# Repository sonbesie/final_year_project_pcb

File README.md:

# Final Year Project: Printed Circuit Board (PCB)

## Description
The PCB’s for my final year project. The repository contains two folders each containing a PCB. The first PCB is the camera board where all the cameras monitoring the finish line are attached. The second PCB contains the designs for the memory card.

## Open
To open the project download KiCad and open the .pro file.

## Image

A render of the first PCB is provided below:

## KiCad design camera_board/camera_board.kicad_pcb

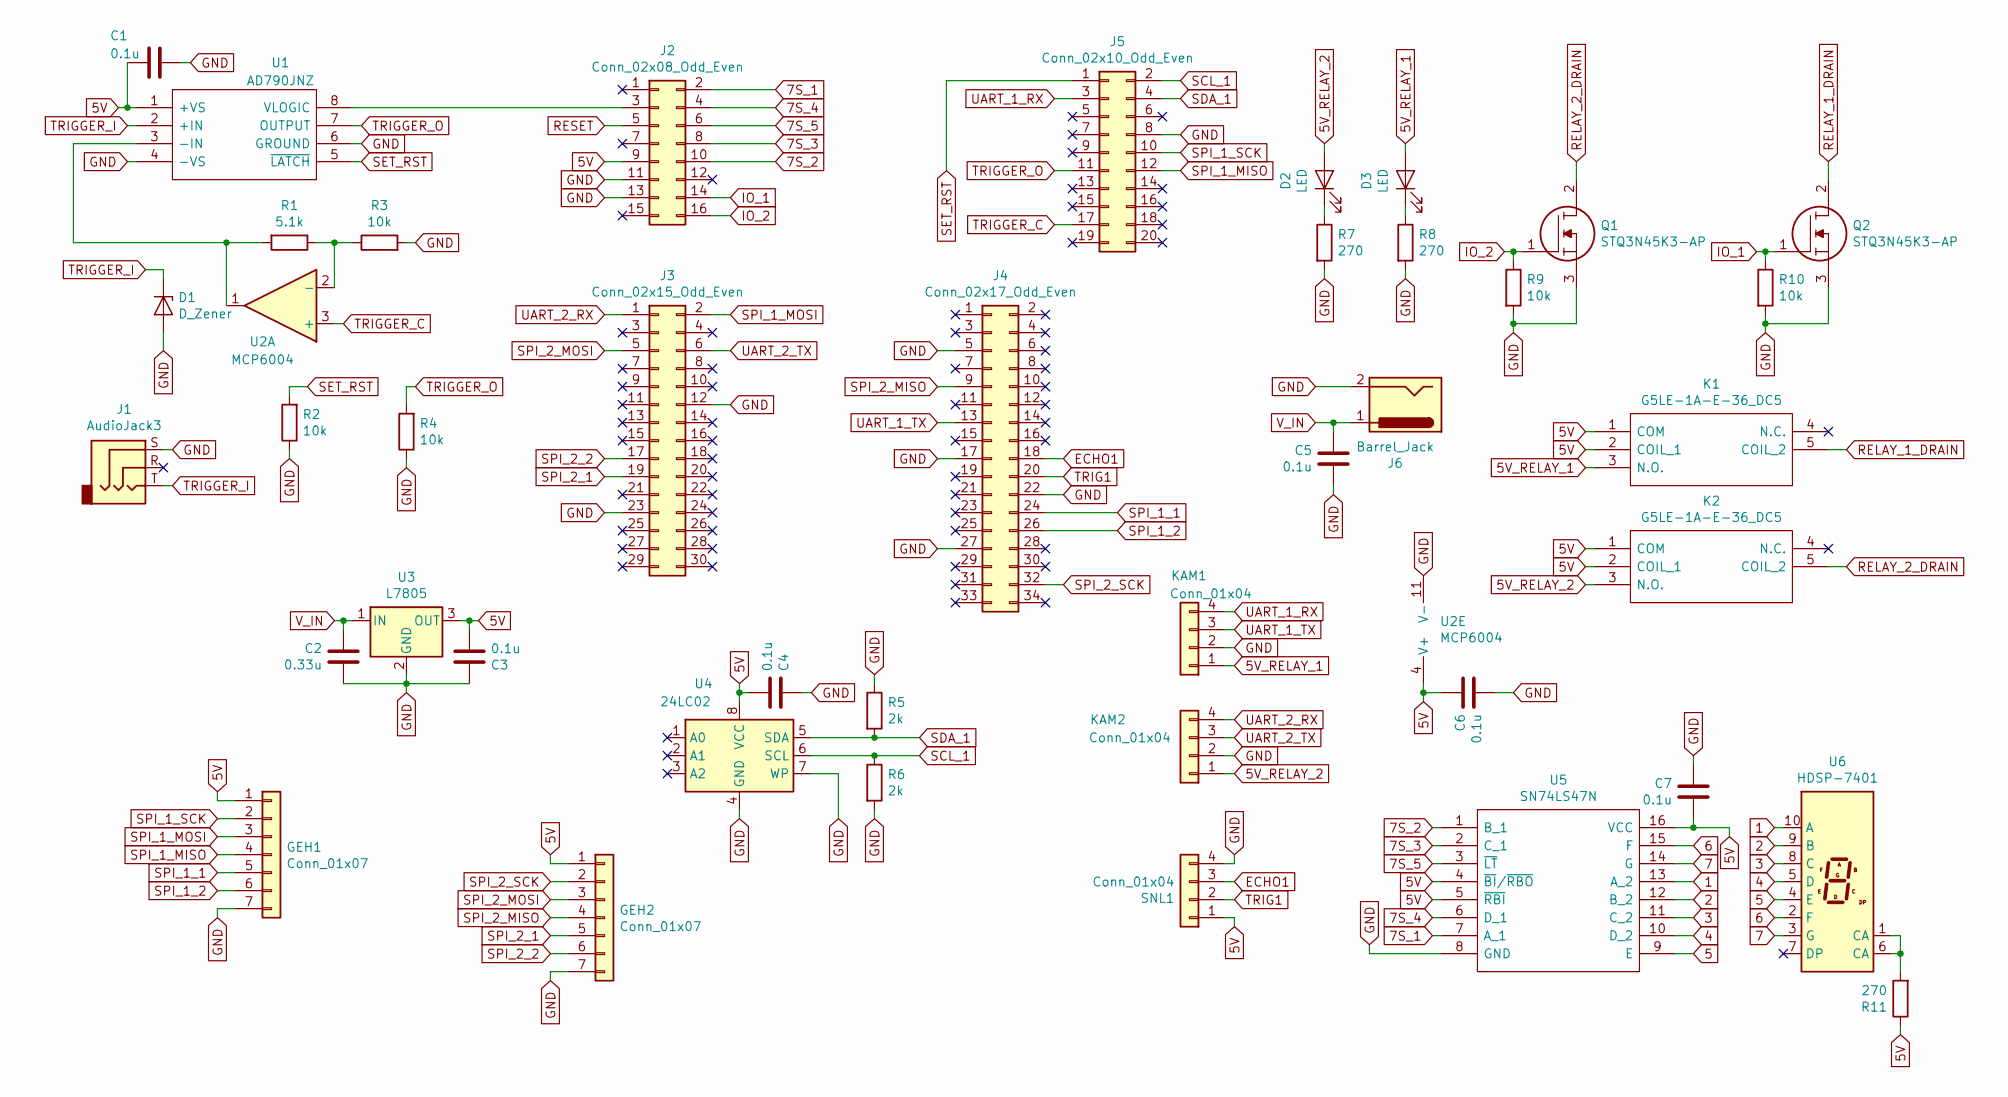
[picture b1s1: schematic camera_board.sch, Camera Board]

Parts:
C1, C3, C4, C5, C6, C7: 0.1u; C_Disc_D5.0mm_W2.5mm_P2.50mm
C2: 0.33u; C_Disc_D5.0mm_W2.5mm_P2.50mm
D1: D_Zener; D_DO-35_SOD27_P2.54mm_Vertical_AnodeUp
D2, D3: LED; LED_D3.0mm
GEH1, GEH2: Conn_01x07; JST_PH_B7B-PH-K_1x07_P2.00mm_Vertical
J1: AudioJack3; Jack_3.5mm_CUI_SJ1-3533NG_Horizontal
J2: Conn_02x08_Odd_Even; PinHeader_2x08_P2.54mm_Vertical
J3: Conn_02x15_Odd_Even; PinHeader_2x15_P2.54mm_Vertical
J4: Conn_02x17_Odd_Even; PinHeader_2x17_P2.54mm_Vertical
J5: Conn_02x10_Odd_Even; PinHeader_2x10_P2.54mm_Vertical
J6: Barrel_Jack; BarrelJack_CUI_PJ-063AH_Horizontal
K1, K2: G5LE-1A-E-36_DC5; G5LE1AE36DC5; Manufacturer_Part_Number G5LE-1A-E-36 DC5; Mouser Part Number 653-G5LE-1A-E-36DC5
KAM1, KAM2: Conn_01x04; JST_PH_B4B-PH-K_1x04_P2.00mm_Vertical
Q1, Q2: STQ3N45K3-AP; TO-92_Inline_Wide; Manufacturer_Part_Number STQ3N45K3-AP; Mouser Part Number 511-STQ3N45K3-AP
R1: 5.1k; R_Axial_DIN0207_L6.3mm_D2.5mm_P7.62mm_Horizontal
R2, R3, R4, R9, R10: 10k; R_Axial_DIN0207_L6.3mm_D2.5mm_P7.62mm_Horizontal
R5, R6: 2k; R_Axial_DIN0207_L6.3mm_D2.5mm_P7.62mm_Horizontal
R7, R8, R11: 270; R_Axial_DIN0207_L6.3mm_D2.5mm_P7.62mm_Horizontal
SNL1: Conn_01x04; JST_PH_B4B-PH-K_1x04_P2.00mm_Vertical
U1: AD790JNZ; DIP-8_W7.62mm; Manufacturer_Part_Number AD790JNZ; Mouser Part Number 584-AD790JNZ
U2: MCP6004; DIP-14_W7.62mm
U3: L7805; TO-220-3_Vertical
U4: 24LC02; DIP-8_W7.62mm
U5: SN74LS47N; DIP-16_W7.62mm; Manufacturer_Part_Number SN74LS47N; Mouser Part Number 595-SN74LS47N
U6: HDSP-7401

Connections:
1: U5.13 (A_2), U6.10 (A)
2: U5.12 (B_2), U6.9 (B)
3: U5.11 (C_2), U6.8 (C)
4: U5.10 (D_2), U6.5 (D)
5: U5.9 (E), U6.4 (E)
5V: C1.2, C3.2, C4.2, C6.1, C7.2, GEH1.1, GEH2.1, J2.9, K1.1 (COM), K1.2 (COIL_1), K2.1 (COM), K2.2 (COIL_1), R11.1, SNL1.1, U1.1 (+VS), U2.4 (V+), U3.3 (OUT), U4.8 (VCC), U5.4 (~BI~/~RBO), U5.5 (~RBI), U5.16 (VCC)
5V_RELAY_1: D3.2 (A), K1.3 (N.O.), KAM1.1
5V_RELAY_2: D2.2 (A), K2.3 (N.O.), KAM2.1
6: U5.15 (F), U6.2 (F)
7: U5.14 (G), U6.3 (G)
7S_1: J2.2, U5.7 (A_1)
7S_2: J2.10, U5.1 (B_1)
7S_3: J2.8, U5.2 (C_1)
7S_4: J2.4, U5.6 (D_1)
7S_5: J2.6, U5.3 (~LT)
ECHO1: J4.18, SNL1.3
GND: C1.1, C2.2, C3.1, C4.1, C5.2, C6.2, C7.1, D1.2 (A), GEH1.7, GEH2.7, J1.S, J2.11, J2.13, J3.12, J3.23, J4.5, J4.17, J4.22, J4.27, J5.8, J6.2, KAM1.2, KAM2.2, Q1.3, Q2.3, R2.1, R3.2, R4.1, R5.1, R6.2, R7.2, R8.2, R9.2, R10.2, SNL1.4, U1.4 (-VS), U1.6 (GROUND), U2.11 (V-), U3.2 (GND), U4.4 (GND), U4.7 (WP), U5.8 (GND)
IO_1: J2.14, Q2.1, R10.1
IO_2: J2.16, Q1.1, R9.1
unnamed: D2.1 (K), R7.1
unnamed: D3.1 (K), R8.1
unnamed: J2.3, U1.8 (VLOGIC)
unnamed: R1.1, R3.1, U2.2 (-)
unnamed: R1.2, U1.3 (-IN), U2.1
unnamed: R11.2, U6.1 (CA), U6.6 (CA)
RELAY_1_DRAIN: K1.5 (COIL_2), Q2.2
RELAY_2_DRAIN: K2.5 (COIL_2), Q1.2
SCL_1: J5.2, R6.1, U4.6 (SCL)
SDA_1: J5.4, R5.2, U4.5 (SDA)
SET_RST: J5.1, R2.2, U1.5 (~LATCH)
SPI_1_1: GEH1.5, J4.24
SPI_1_2: GEH1.6, J4.26
SPI_1_MISO: GEH1.4, J5.12
SPI_1_MOSI: GEH1.3, J3.2
SPI_1_SCK: GEH1.2, J5.10
SPI_2_1: GEH2.5, J3.19
SPI_2_2: GEH2.6, J3.17
SPI_2_MISO: GEH2.4, J4.9
SPI_2_MOSI: GEH2.3, J3.5
SPI_2_SCK: GEH2.2, J4.32
TRIG1: J4.20, SNL1.2
TRIGGER_C: J5.17, U2.3 (+)
TRIGGER_I: D1.1 (K), J1.T, U1.2 (+IN)
TRIGGER_O: J5.11, R4.2, U1.7 (OUTPUT)
UART_1_RX: J5.3, KAM1.4
UART_1_TX: J4.13, KAM1.3
UART_2_RX: J3.1, KAM2.4
UART_2_TX: J3.6, KAM2.3
V_IN: C2.1, C5.1, J6.1, U3.1 (IN)

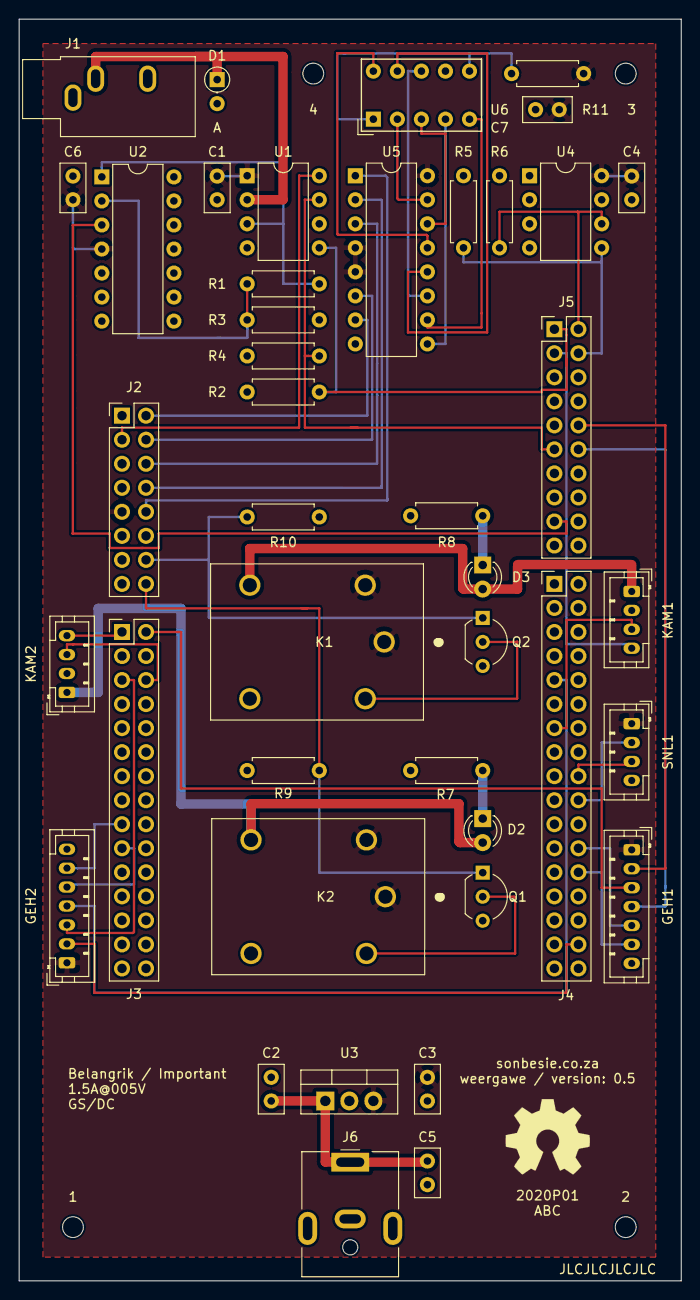
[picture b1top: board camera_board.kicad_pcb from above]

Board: 2 copper layers, 70.0 x 133.4 mm, 46 parts (0 on the bottom side), 49 nets.

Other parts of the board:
1, 2, 3, 4: MountingHole_2.2mm_M2

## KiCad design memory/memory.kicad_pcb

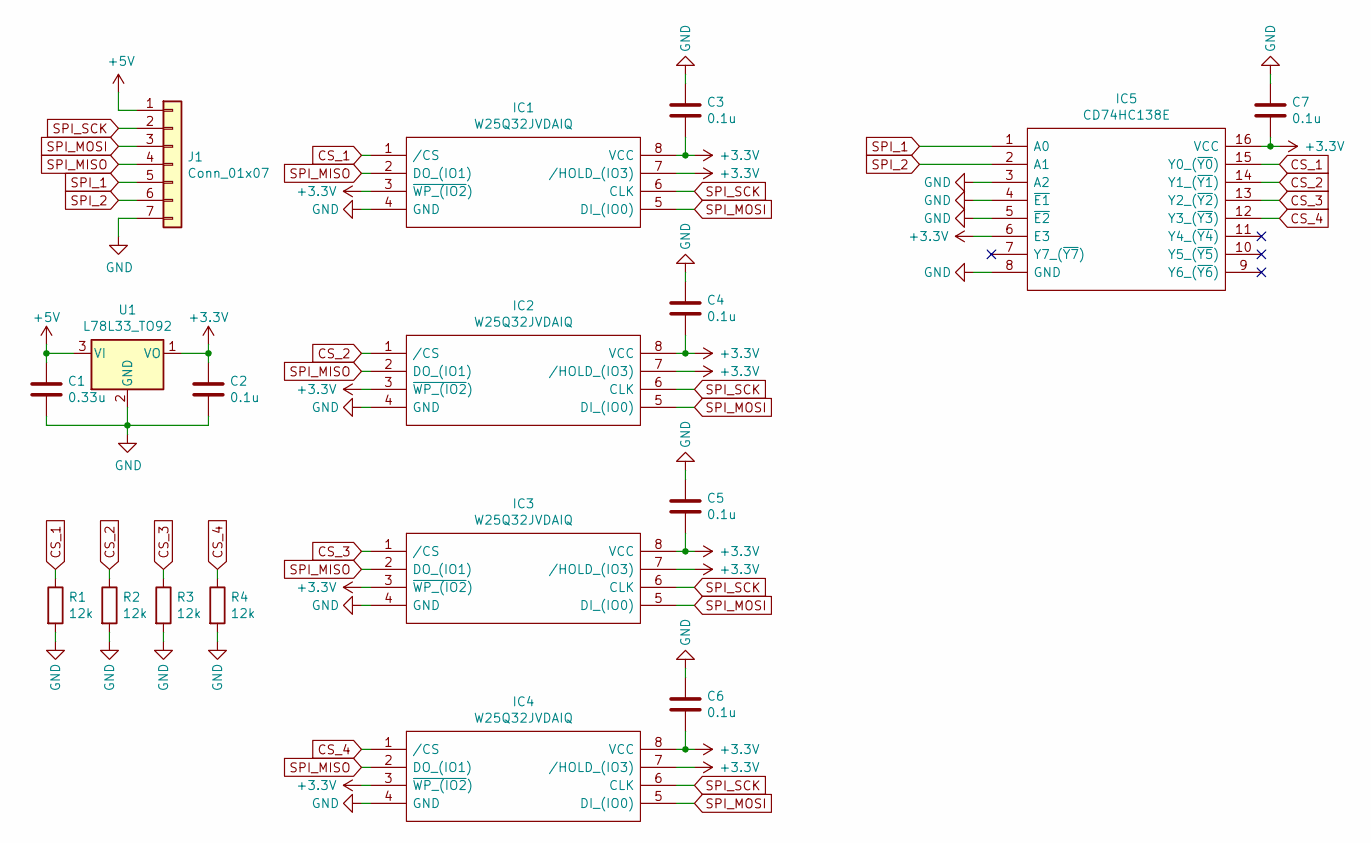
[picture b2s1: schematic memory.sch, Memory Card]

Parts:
C1: 0.33u; C_Disc_D5.0mm_W2.5mm_P2.50mm
C2, C3, C4, C5, C6, C7: 0.1u; C_Disc_D5.0mm_W2.5mm_P2.50mm
IC1, IC2, IC3, IC4: W25Q32JVDAIQ; DIP-8_W7.62mm; Manufacturer_Part_Number W25Q32JVDAIQ; Mouser Part Number 454-W25Q32JVDAIQ
IC5: CD74HC138E; DIP-16_W7.62mm; Manufacturer_Part_Number CD74HC138E; Mouser Part Number 595-CD74HC138E
J1: Conn_01x07; JST_PH_B7B-PH-K_1x07_P2.00mm_Vertical
R1, R2, R3, R4: 12k; R_Axial_DIN0207_L6.3mm_D2.5mm_P7.62mm_Horizontal
U1: L78L33_TO92; TO-92_Inline

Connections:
+3V3: C2.1, C3.2, C4.2, C5.2, C6.2, C7.2, IC1.3 (~WP_(IO2)), IC1.7 (/HOLD_(IO3)), IC1.8 (VCC), IC2.3 (~WP_(IO2)), IC2.7 (/HOLD_(IO3)), IC2.8 (VCC), IC3.3 (~WP_(IO2)), IC3.7 (/HOLD_(IO3)), IC3.8 (VCC), IC4.3 (~WP_(IO2)), IC4.7 (/HOLD_(IO3)), IC4.8 (VCC), IC5.6 (E3), IC5.16 (VCC), U1.1 (VO)
+5V: C1.1, J1.1, U1.3 (VI)
CS_1: IC1.1 (/CS), IC5.15 (Y0_(~Y0)), R1.1
CS_2: IC2.1 (/CS), IC5.14 (Y1_(~Y1)), R2.1
CS_3: IC3.1 (/CS), IC5.13 (Y2_(~Y2)), R3.1
CS_4: IC4.1 (/CS), IC5.12 (Y3_(~Y3)), R4.1
GND: C1.2, C2.2, C3.1, C4.1, C5.1, C6.1, C7.1, IC1.4 (GND), IC2.4 (GND), IC3.4 (GND), IC4.4 (GND), IC5.3 (A2), IC5.4 (~E1), IC5.5 (~E2), IC5.8 (GND), J1.7, R1.2, R2.2, R3.2, R4.2, U1.2 (GND)
SPI_1: IC5.1 (A0), J1.5
SPI_2: IC5.2 (A1), J1.6
SPI_MISO: IC1.2 (DO_(IO1)), IC2.2 (DO_(IO1)), IC3.2 (DO_(IO1)), IC4.2 (DO_(IO1)), J1.4
SPI_MOSI: IC1.5 (DI_(IO0)), IC2.5 (DI_(IO0)), IC3.5 (DI_(IO0)), IC4.5 (DI_(IO0)), J1.3
SPI_SCK: IC1.6 (CLK), IC2.6 (CLK), IC3.6 (CLK), IC4.6 (CLK), J1.2

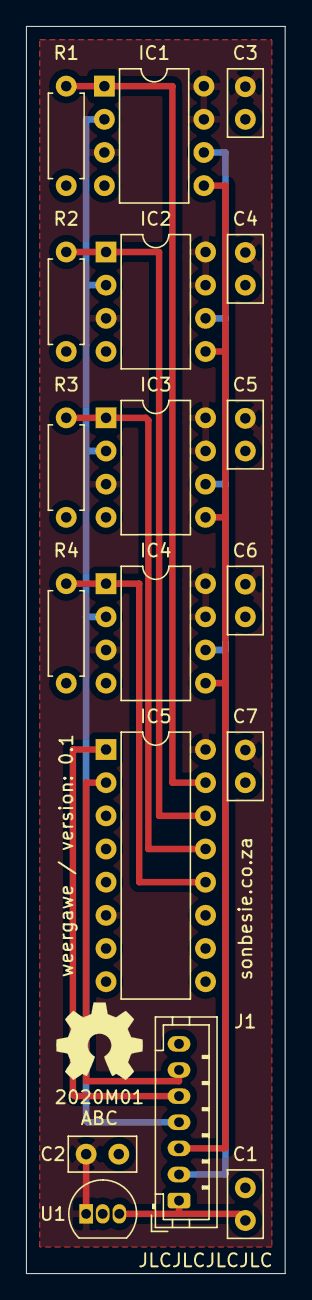
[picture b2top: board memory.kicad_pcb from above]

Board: 2 copper layers, 19.8 x 95.5 mm, 18 parts (0 on the bottom side), 12 nets.

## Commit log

2021-03-23 first github commit
2021-03-23 Create README.md
    updated the readme file
2021-03-23 Update README.md
    fixed spelling mistake
2021-03-23 Update README.md
    updated the readme file
